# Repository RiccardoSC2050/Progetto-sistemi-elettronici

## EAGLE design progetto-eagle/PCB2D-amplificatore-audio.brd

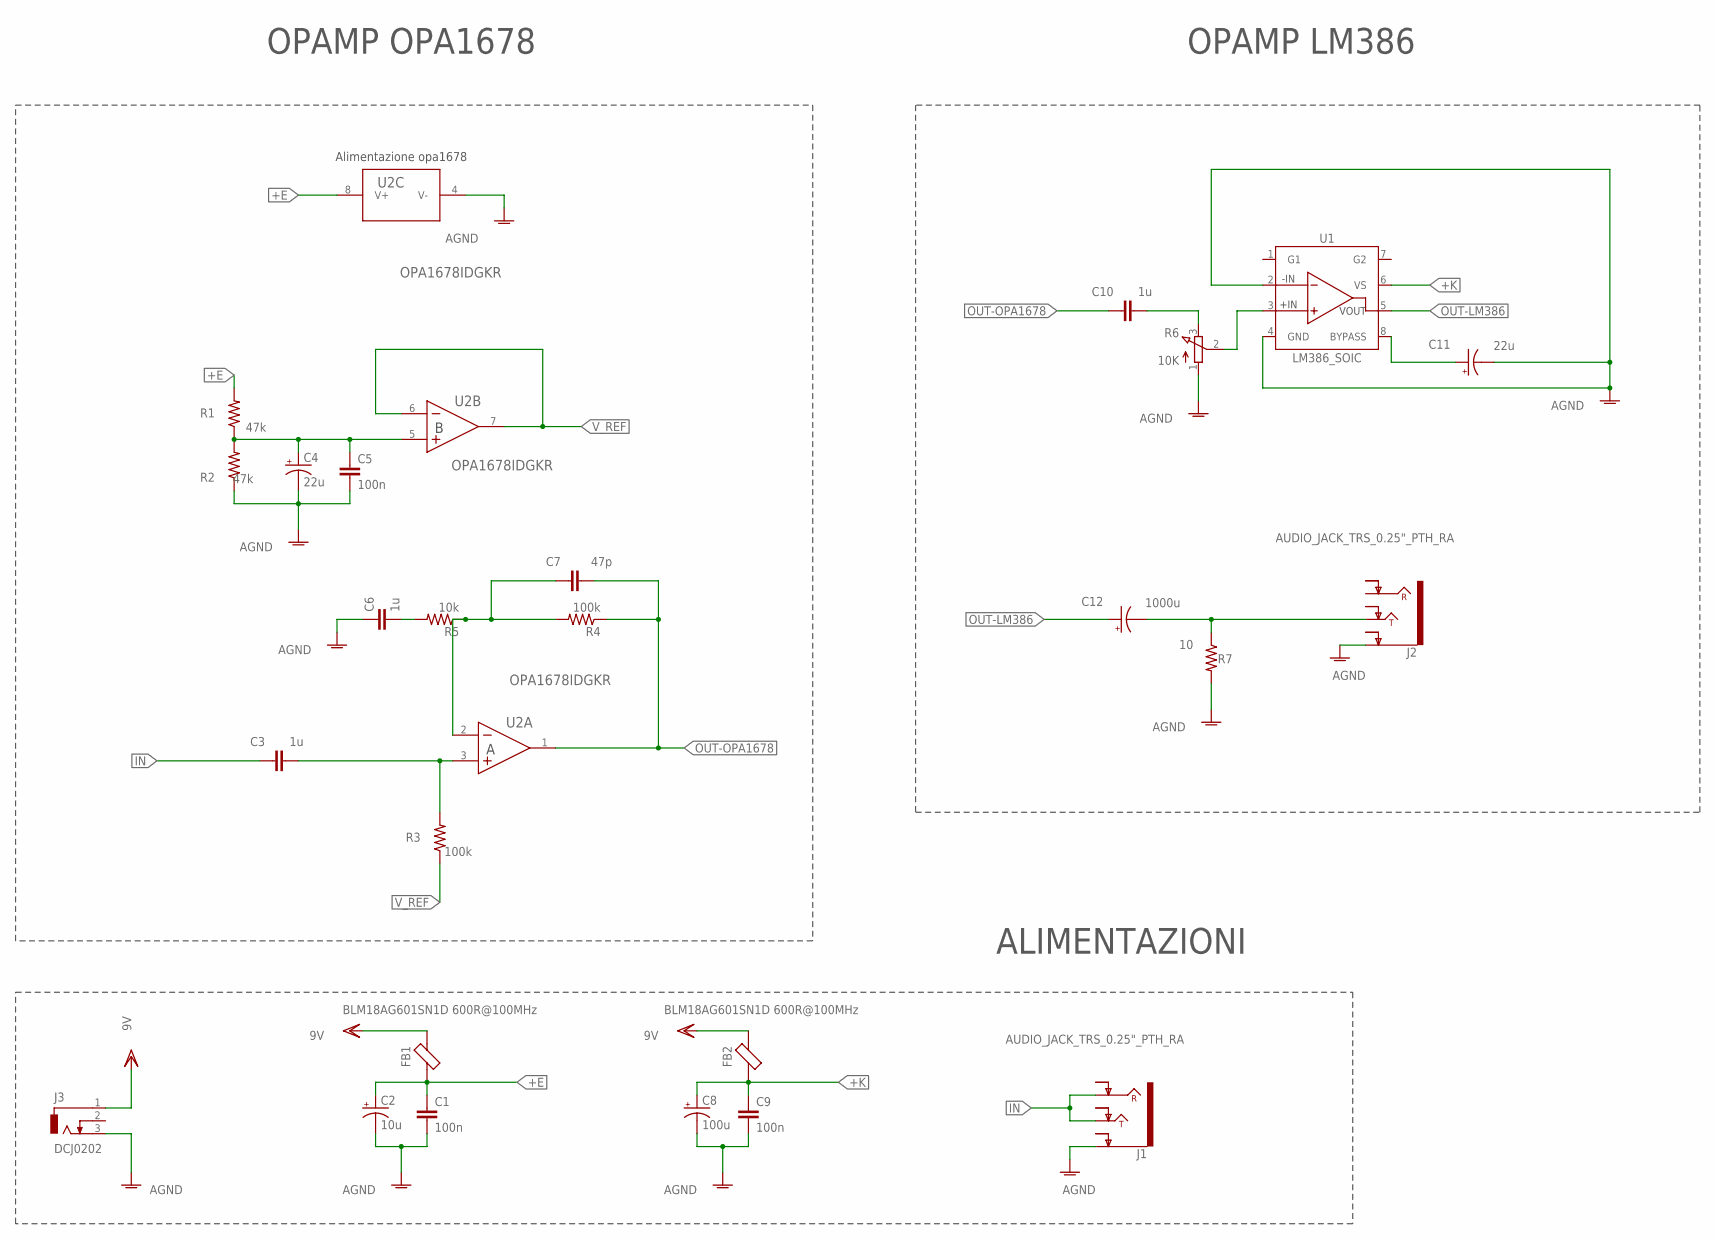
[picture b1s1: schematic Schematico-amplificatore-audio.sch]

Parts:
C1, C5, C9: 100n; C0603
C2: 10u; CT3216
C3, C6, C10: 1u; C0603
C4, C11: 22u; CT3216
C7: 47p; C0603
C8: 100u; CT3216
C12: 1000u; CT3216
FB1, FB2: BLM18AG601SN1D 600R@100MHz; BEADC1608X95N
J1, J2: AUDIO_JACK_TRS_0.25"_PTH_RA; AUDIO_JACK_0.25"_TRS_PTH_RA
J3: DCJ0202
R1, R2: 47k; R0603
R3, R4: 100k; R0603
R5: 10k; R0603
R6: 10K; 3RP/1610N
R7: 10; R0603
U1: LM386_SOIC; SOIC127P600X175-8N
U2: OPA1678IDGKR; DGK0008A_N

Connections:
+E: C1.1, C2.+, FB1.1, R1.2, U2.8 (V+)
+K: C8.+, C9.1, FB2.1, U1.6 (VS)
AGND: C1.2, C2.-, C4.-, C5.2, C6.1, C8.-, C9.2, C11.-, J1.SLEEVE (EARTH), J2.SLEEVE (EARTH), J3.3, R2.1, R6.1 (A), R7.2, U1.2 (-IN), U1.4 (GND), U2.4 (V-)
IN: C3.1, J1.RING, J1.TIP
unnamed: C11.+, U1.8 (BYPASS)
unnamed: C4.+, C5.1, R1.1, R2.2, U2.5 (IN+)
unnamed: R6.2 (S), U1.3 (+IN)
unnamed: C3.2, R3.2, U2.3 (IN+)
unnamed: C12.-, J2.TIP, R7.1
unnamed: C7.1, R4.2, R5.1, U2.2 (IN-)
unnamed: C6.2, R5.2
unnamed: C10.2, R6.3 (E)
OUT-LM386: C12.+, U1.5 (VOUT)
OUT-OPA1678: C7.2, C10.1, R4.1, U2.1 (OUT)
VDD: FB1.2, FB2.2, J3.1
V_REF: R3.1, U2.6 (IN-), U2.7 (OUT)

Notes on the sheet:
Alimentazione opa1678
OPAMP OPA1678
ALIMENTAZIONI
OPAMP LM386

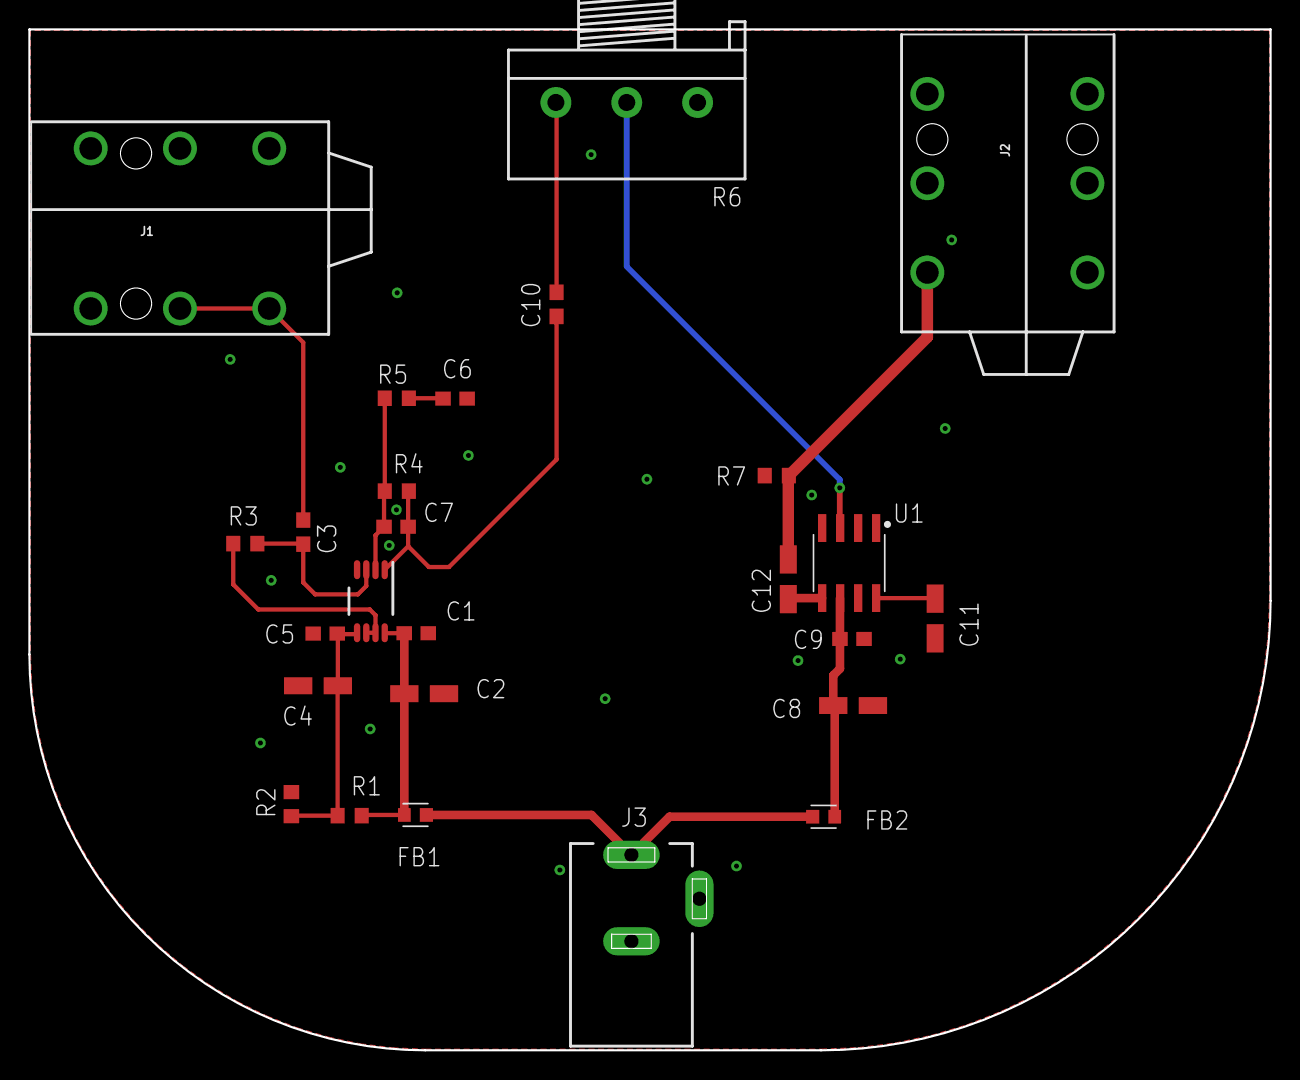
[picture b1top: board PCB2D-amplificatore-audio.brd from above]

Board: 2 copper layers, 87.6 x 72.1 mm, 26 parts (0 on the bottom side), 16 nets.

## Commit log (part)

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2026-05-08 test
2026-05-08 passivo rc
    guadagno
2026-05-12 tutto il passivo
2026-05-15 attivo ideale
2026-05-19 rc attivo reale
2026-05-20 carichi reale
2026-05-27 inizio presentazione
    inizio presentazione
2026-06-01 miglioramento presentazione e immagini
2026-06-02 conclusione foto
    foto aggiornate e pwt poco definito
2026-06-04 aggiornamento sviluppo progetto
    presentazione e schemi aggiornati
2026-06-06 rc ideale aggiornato
2026-06-25 aggiornamento powerpoint
    fini ideale attivo
2026-06-26 piccole modifiche
2026-06-26 completamento presentazione
    nuovo design
2026-06-28 fine presentazione raccoglimento dati
2026-06-28 repush della presentaziuone completa
2026-06-29 impostazione eagle
    schematico pcb amplificatore audio

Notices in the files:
parts and their libraries:
SparkFun-Connectors: Licensing: Creative Commons ShareAlike 4.0 International - https://creativecommons.org/licenses/by-sa/4.0
COPYRIGHT: Copyright (C) 2026 Ultra Librarian. All rights reserved.
